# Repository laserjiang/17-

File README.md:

拿开源资料做的一个小键盘，用来打电脑的模拟游戏，防止把笔记本的键盘弄坏。详细视频可以看
https://www.bilibili.com/video/BV1sT4y1y7c5?spm_id_from=333.999.0.0

还有一部分安装软件，可以去百度云盘
链接: https://pan.baidu.com/s/1Q_vZ9K_aPjOmQgbRjwy3_w?pwd=iqhj 提取码: iqhj 复制这段内容后打开百度网盘手机App，操作更方便哦

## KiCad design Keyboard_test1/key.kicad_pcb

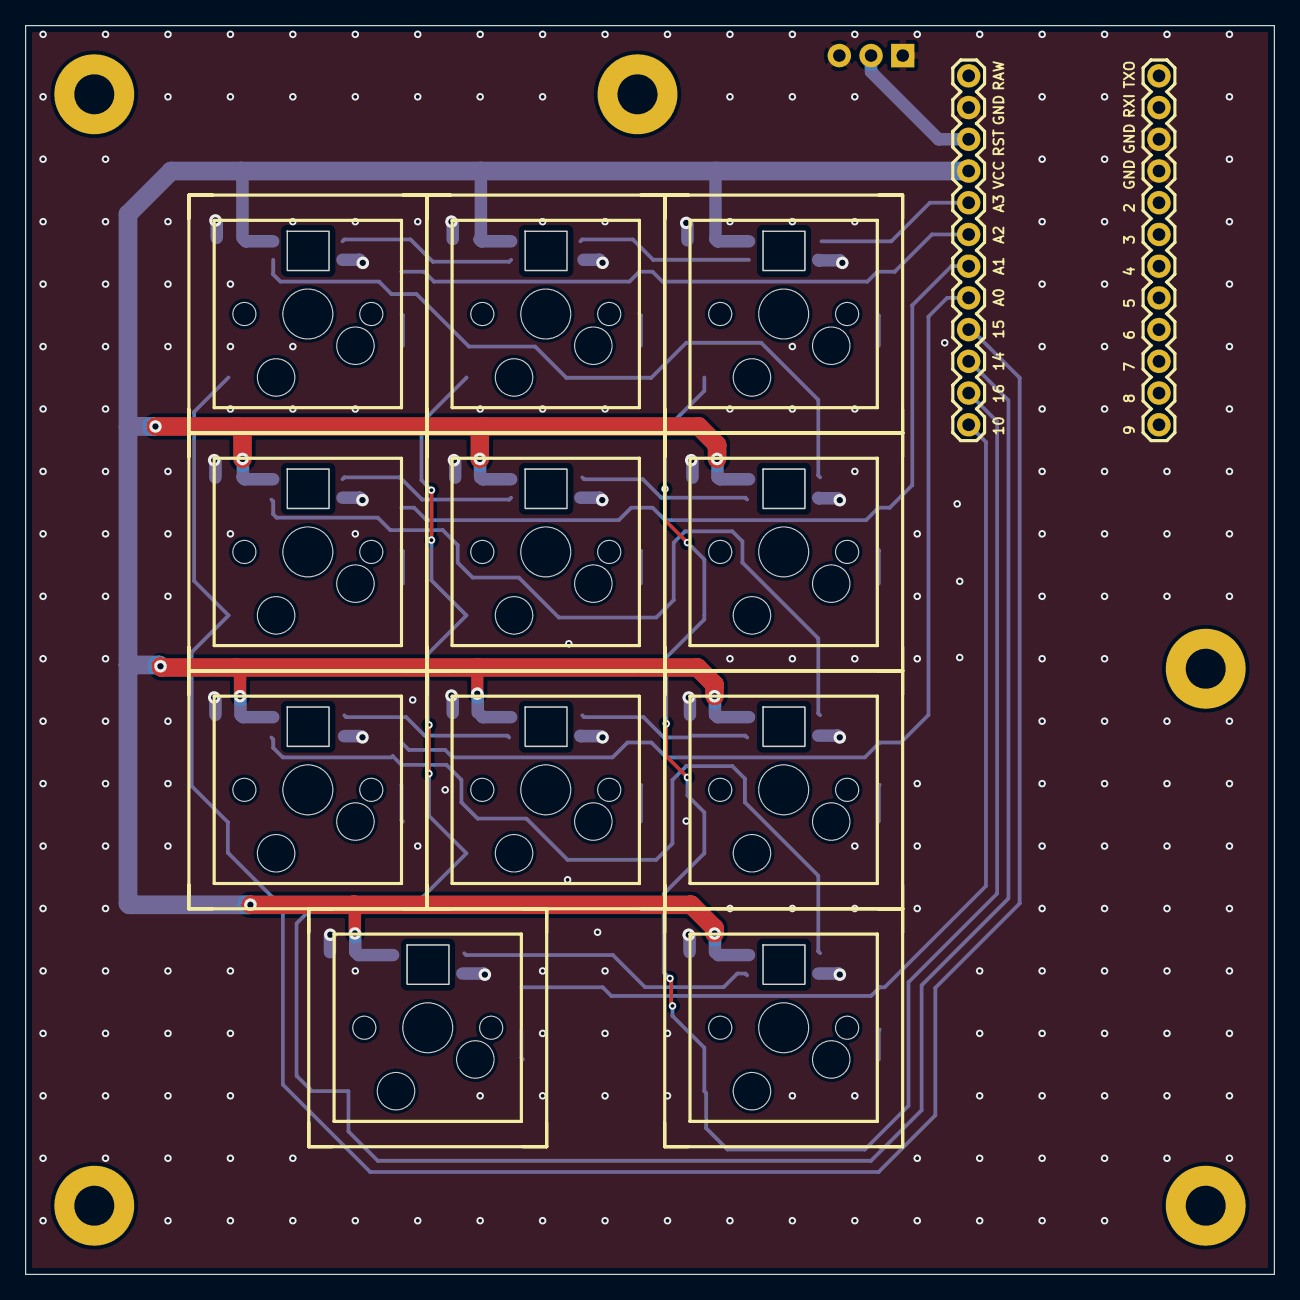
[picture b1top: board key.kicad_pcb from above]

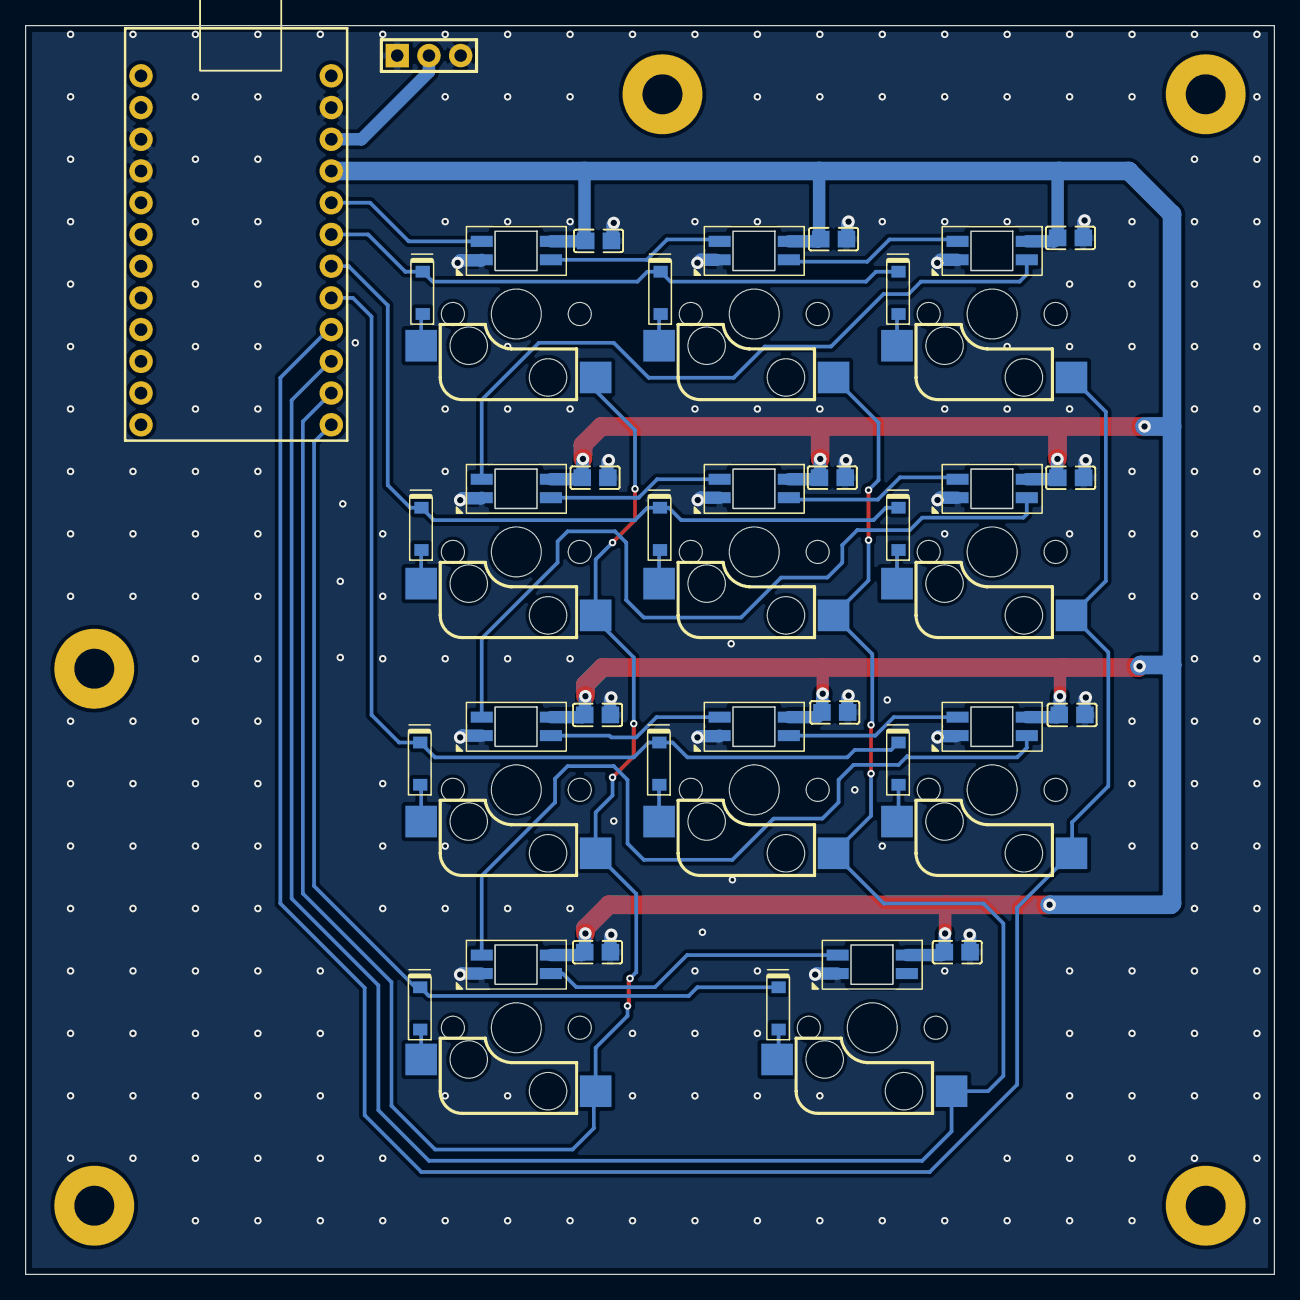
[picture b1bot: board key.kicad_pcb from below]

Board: 2 copper layers, 100.0 x 100.0 mm, 35 parts (24 on the bottom side), 32 nets.

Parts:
C1, C2, C3, C4, C5, C6, C7, C8, C9, C10, C11: 100n; C0805
D1, D2, D3, D4, D5, D6, D7, D8, D9, D10, D11: 1N4148W; SOD-123_L2.8-W1.8-LS3.7-RD
J1: lceda; 排针3P
P1: Pro_Micro_-_5V; Arduino_PRO_MICRO
SW1, SW2, SW3, SW4, SW5, SW6, SW7, SW8, SW9, SW10, SW11: lceda; 凯华轴座+3528反贴灯

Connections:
+5V: C1.2, C2.2, C3.2, C4.2, C5.2, C6.2, C7.2, C8.2, C9.2, C10.2, C11.2, P1.16 (VCC), SW1.1, SW2.1, SW3.1, SW4.1, SW5.1, SW6.1, SW7.1, SW8.1, SW9.1, SW10.1, SW11.1
/reset: J1.2, P1.15 (RST)
GND: C1.1, C2.1, C3.1, C4.1, C5.1, C6.1, C7.1, C8.1, C9.1, C10.1, C11.1, J1.1, J1.3, P1.9 (GND), P1.10 (GND), P1.14 (GND), SW1.5, SW2.5, SW3.5, SW4.5, SW5.5, SW6.5, SW7.5, SW8.5, SW9.5, SW10.5, SW11.5
unnamed: D1.2 (A), SW1.4
unnamed: D2.2 (A), SW2.4
unnamed: D3.2 (A), SW3.4
unnamed: D4.2 (A), SW4.4
unnamed: D5.2 (A), SW5.4
unnamed: D6.2 (A), SW6.4
unnamed: D7.2 (A), SW7.4
unnamed: D8.2 (A), SW8.4
unnamed: D9.2 (A), SW9.4
unnamed: D10.2 (A), SW10.4
unnamed: D11.2 (A), SW11.4
unnamed: SW1.2, SW6.6
unnamed: SW1.6, SW2.2
unnamed: SW2.6, SW3.2
unnamed: SW4.2, SW9.6
unnamed: SW4.6, SW5.2
unnamed: SW5.6, SW6.2
unnamed: SW7.6, SW8.2
unnamed: SW8.6, SW9.2
unnamed: SW10.6, SW11.2
unnamed: SW7.2, SW11.6
RGB: P1.17 (A3), SW3.6
col0: P1.21 (D15), SW1.3, SW4.3, SW7.3
col1: P1.22 (D14), SW2.3, SW5.3, SW8.3, SW10.3
col2: P1.23 (D16), SW3.3, SW6.3, SW9.3, SW11.3
row0: D1.1 (K), D2.1 (K), D3.1 (K), P1.18 (A2)
row1: D4.1 (K), D5.1 (K), D6.1 (K), P1.19 (A1)
row2: D7.1 (K), D8.1 (K), D9.1 (K), P1.20 (A0)
row3: D10.1 (K), D11.1 (K), P1.24 (D10)
